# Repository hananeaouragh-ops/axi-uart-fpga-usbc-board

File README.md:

# AXI4-Lite UART IP Core & Custom USB-C to UART PCB

An end-to-end embedded hardware design project combining **Verilog RTL development, FPGA synthesis, simulation-based verification, and custom PCB design**.

The project implements an AXI4-Lite UART IP core with transmit and receive FIFOs, a configurable baud rate generator, a self-checking Verilog testbench and a UVM environment. It also includes a custom two-layer USB-C to UART breakout PCB designed in KiCad 10 around the FT232RL USB-to-UART bridge.

> **Project Status:** RTL simulation (Verilog testbench and UVM environment) and FPGA synthesis completed. PCB layout, routing and KiCad DRC completed with 0 errors. Fabrication and hardware validation are still pending.

---

## Table of Contents

- [Key Features](#key-features)
- [System Architecture](#system-architecture)
- [RTL Design](#rtl-design)
- [Verification and Simulation](#verification-and-simulation)
- [FPGA Synthesis Results](#fpga-synthesis-results)
- [Custom USB-C to UART PCB](#custom-usb-c-to-uart-pcb)
- [Visual Showcase](#visual-showcase)
- [Repository Structure](#repository-structure)
- [Getting Started](#getting-started)
- [Current Limitations](#current-limitations)
- [Roadmap](#roadmap)
- [Technologies Used](#technologies-used)
- [License](#license)
- [Author](#author)

---

## Key Features

### FPGA and RTL
- AXI4-Lite slave interface
- UART transmitter and receiver
- Independent TX and RX FIFOs
- Configurable baud rate generator (115200 baud at 100 MHz)
- Modular RTL architecture, targeting Intel Cyclone II

### Verification
- Self-checking Verilog testbench: AXI write, UART TX, loopback, RX FIFO, AXI read-back (test byte `8'hA5`)
- UVM environment (driver, monitor, scoreboard) running in ModelSim: 0 `UVM_ERROR`, 0 `UVM_FATAL`

### PCB Design
- Custom 2-layer USB-C to UART breakout board (65 x 35 mm)
- FT232RL USB-to-UART bridge and AMS1117-3.3 regulator
- GND planes on both copper layers
- Python-assisted netlist generation, placement and design rules
- Freerouting auto-routing, KiCad DRC with 0 errors, 3D visualization

---

## System Architecture

```text
             AXI4-Lite Master
                    |
                    v
          +--------------------+
          |  AXI4-Lite Slave   |
          |  Register Interface|
          +--------------------+
                    |
          +---------+---------+
          |                   |
          v                   v
   +-------------+     +-------------+
   |   TX FIFO   |     |   RX FIFO   |
   +-------------+     +-------------+
          |                   ^
          v                   |
   +-------------+     +-------------+
   |  UART TX    |     |  UART RX    |
   +-------------+     +-------------+
          |                   ^
          v                   |
        TX Pin              RX Pin

          +------------------+
          |  Baud Generator  |
          +------------------+
```

**Transmit path:** AXI4-Lite write, TX FIFO, UART transmitter, TX serial output.

**Receive path:** RX serial input, UART receiver, RX FIFO, AXI4-Lite read.

**Loopback:** in simulation, the TX output is connected to the RX input to verify that transmitted data is received correctly.

---

## RTL Design

| Module | Responsibility |
|---|---|
| `axi_uart_top.v` | Top-level integration and AXI4-Lite interface |
| `uart_tx.v` | UART serial transmission |
| `uart_rx.v` | UART serial reception |
| `baud_gen.v` | Baud timing generation |
| `fifo.v` | Data buffering (8-bit, 16 entries) |
| `tb_axi_uart.v` | Self-checking simulation testbench |

| Parameter | Value |
|---|---|
| Reference clock | 100 MHz |
| Baud rate | 115200 |
| AXI data width | 32 bit (UART data on bits [7:0]) |
| FIFO | 8-bit data, 16 entries |
| FPGA family | Intel Cyclone II |

---

## Verification and Simulation

### Verilog testbench

| Test | Objective |
|---|---|
| AXI write | Write a byte through the AXI4-Lite bus |
| UART TX | Verify serial transmission |
| Loopback | Verify transmitted and received data match |
| RX FIFO | Verify received data buffering |
| AXI read-back | Read the byte back through the bus |

Expected output:

```text
[TB SUCCESS] Loopback Data Matched: 0xa5
```

### UVM environment

The UVM environment (agent with sequencer, driver and monitor, scoreboard, environment and test) runs in ModelSim with these results:

```text
UVM_INFO    : 14
UVM_WARNING : 0
UVM_ERROR   : 0
UVM_FATAL   : 0
[SCOREBOARD] : 10 reports
```

### Running the simulation (ModelSim)

From the project root:

```tcl
vlog rtl/baud_gen.v rtl/fifo.v rtl/uart_rx.v rtl/uart_tx.v rtl/axi_uart_top.v
vlog rtl/tb_axi_uart.v
vsim -voptargs="+acc" tb_axi_uart
add wave -r /*
run -all
```

UVM test:

```tcl
vlog -sv +incdir+sim/uvm_tb sim/uvm_tb/axi_uart_if.sv
vlog -sv +incdir+sim/uvm_tb sim/uvm_tb/tb_top.sv
vsim -voptargs="+acc" tb_top +UVM_TESTNAME=axi_uart_test
run -all
```

---

## FPGA Synthesis Results

Synthesized for the Intel Cyclone II `EP2C5F256C6` with Quartus II.

| Parameter | Result |
|---|---:|
| Logic Elements | 196 / 4,608 (about 4%) |
| Registers | 124 |
| Maximum Frequency (Fmax) | 189.72 MHz |

The Fmax value is a synthesis timing-analysis result for the configured design and constraints; it has not been validated on hardware.

---

## Custom USB-C to UART PCB

| Ref | Component | Function |
|---|---|---|
| J1 | USB-C receptacle | USB connection and power input |
| U2 | FT232RL | USB-to-UART conversion |
| U1 | AMS1117-3.3 | 3.3 V regulation |
| C1, C2 | SMD capacitors | Decoupling |
| J2 | 1x6 pin header | UART connection to the FPGA board |

### Design workflow

1. Netlist generation with Python (`make_netlist.py`)
2. Board outline, placement, design rules and GND planes scripted with KiCad's Python API
3. Auto-routing with Freerouting (Specctra DSN/SES exchange)
4. KiCad DRC: 0 errors
5. 3D visualization with component models

---

## Visual Showcase

### 1. FPGA Synthesis Report (Quartus II)

### 2. RTL Architecture (Quartus RTL Viewer)

### 3. Custom USB-C to UART PCB (KiCad 10, 3D render)

### 4. Simulation Waveform (ModelSim SE-64)

### 5. UVM Report Summary (ModelSim SE-64)

---

## Repository Structure

```text
.
├── rtl/       Verilog sources and testbench
├── sim/       UVM environment (sim/uvm_tb)
├── pcb/       KiCad project and Python scripts
├── docs/      Screenshots
├── LICENSE
└── README.md
```

---

## Getting Started

### Requirements

- Intel Quartus II (Cyclone II support)
- ModelSim (Verilog and SystemVerilog/UVM)
- KiCad 10
- Freerouting
- Python (KiCad scripting console)

### Clone

```bash
git clone https://github.com/hananeaouragh-ops/axi-uart-fpga-usbc-board.git
cd axi-uart-fpga-usbc-board
```

### Open the PCB project

1. Open the `.kicad_pro` file in `pcb/` with KiCad 10.
2. Inspect the layout, run DRC and open the 3D viewer.

---

## Current Limitations

- The UVM environment is a first version: limited stimulus, no functional coverage yet.
- AXI4-Lite protocol compliance has not been checked exhaustively.
- The PCB has not been fabricated, and no physical UART communication has been tested.
- Fmax comes from synthesis timing analysis, not from hardware measurements.

---

## Roadmap

- [x] Verilog RTL and self-checking testbench
- [x] FPGA synthesis (Cyclone II)
- [x] UVM environment (driver, monitor, scoreboard)
- [x] PCB layout, routing and DRC
- [ ] Add functional coverage and more UVM sequences
- [ ] Verify FIFO overflow/underflow and reset scenarios
- [ ] Generate manufacturing files (Gerber, drill, BOM) and fabricate the PCB
- [ ] Hardware test: UART loopback and FPGA-to-PC communication

---

## Technologies Used

| Category | Technologies |
|---|---|
| RTL Design | Verilog HDL |
| Bus Interface | AXI4-Lite |
| Simulation / Verification | ModelSim, Verilog testbench, SystemVerilog UVM |
| FPGA | Intel Quartus II, Cyclone II |
| PCB Design | KiCad 10, Freerouting |
| Automation | Python |

---

## License

Released under the MIT License (see [LICENSE](LICENSE)).

---

## Author

**Hanane Aouragh**

Embedded Systems | FPGA Design | Digital Hardware | PCB Design

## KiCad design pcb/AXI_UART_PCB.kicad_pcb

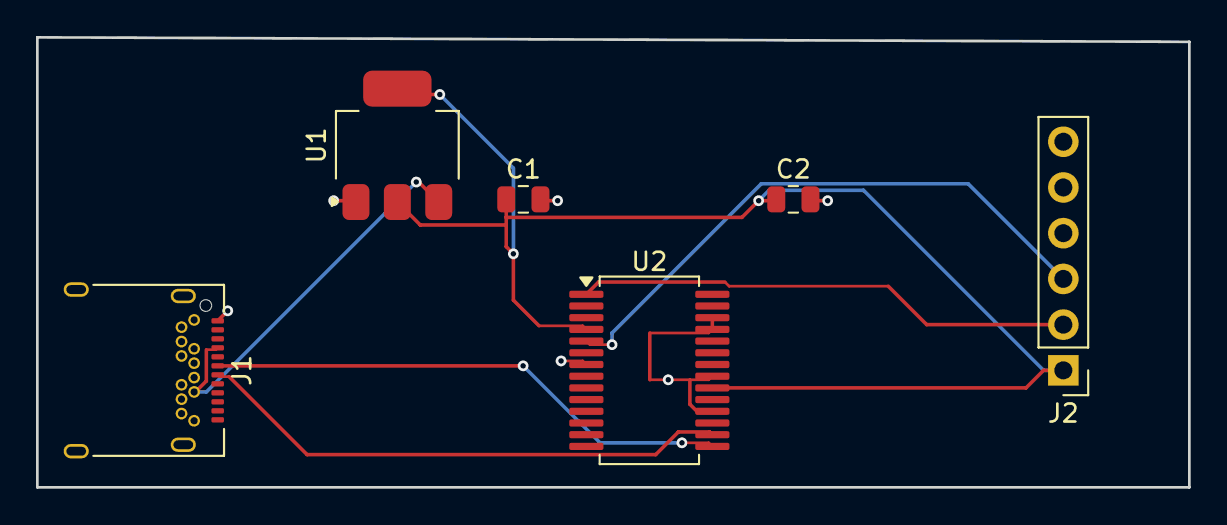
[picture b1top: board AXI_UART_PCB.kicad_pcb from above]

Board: 2 copper layers, 64.0 x 25.0 mm, 6 parts (0 on the bottom side), 7 nets.

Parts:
C1, C2: C; C_0805_2012Metric
J1: USB_C; USB_C_Receptacle_Amphenol_12401548E4-2A
J2: Conn_01x06_Pin; PinHeader_1x06_P2.54mm_Vertical
U1: AMS1117-3.3; SOT-223-3_TabPin2
U2: FT232RL; SSOP-28_5.3x10.2mm_P0.65mm

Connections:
+3V3: C1.1, C2.1, J2.1, U1.2, U2.4, U2.20
GND: C1.2, C2.2, J1.A1, J1.B1, J2.6, U1.1, U2.7, U2.18, U2.21, U2.25, U2.26
UART_RX: J2.3, U2.5
UART_TX: J2.2, U2.1
USB_DN: J1.A7, U2.16
USB_DP: J1.A6, U2.15
VBUS: J1.A4, J1.B4, U1.3
